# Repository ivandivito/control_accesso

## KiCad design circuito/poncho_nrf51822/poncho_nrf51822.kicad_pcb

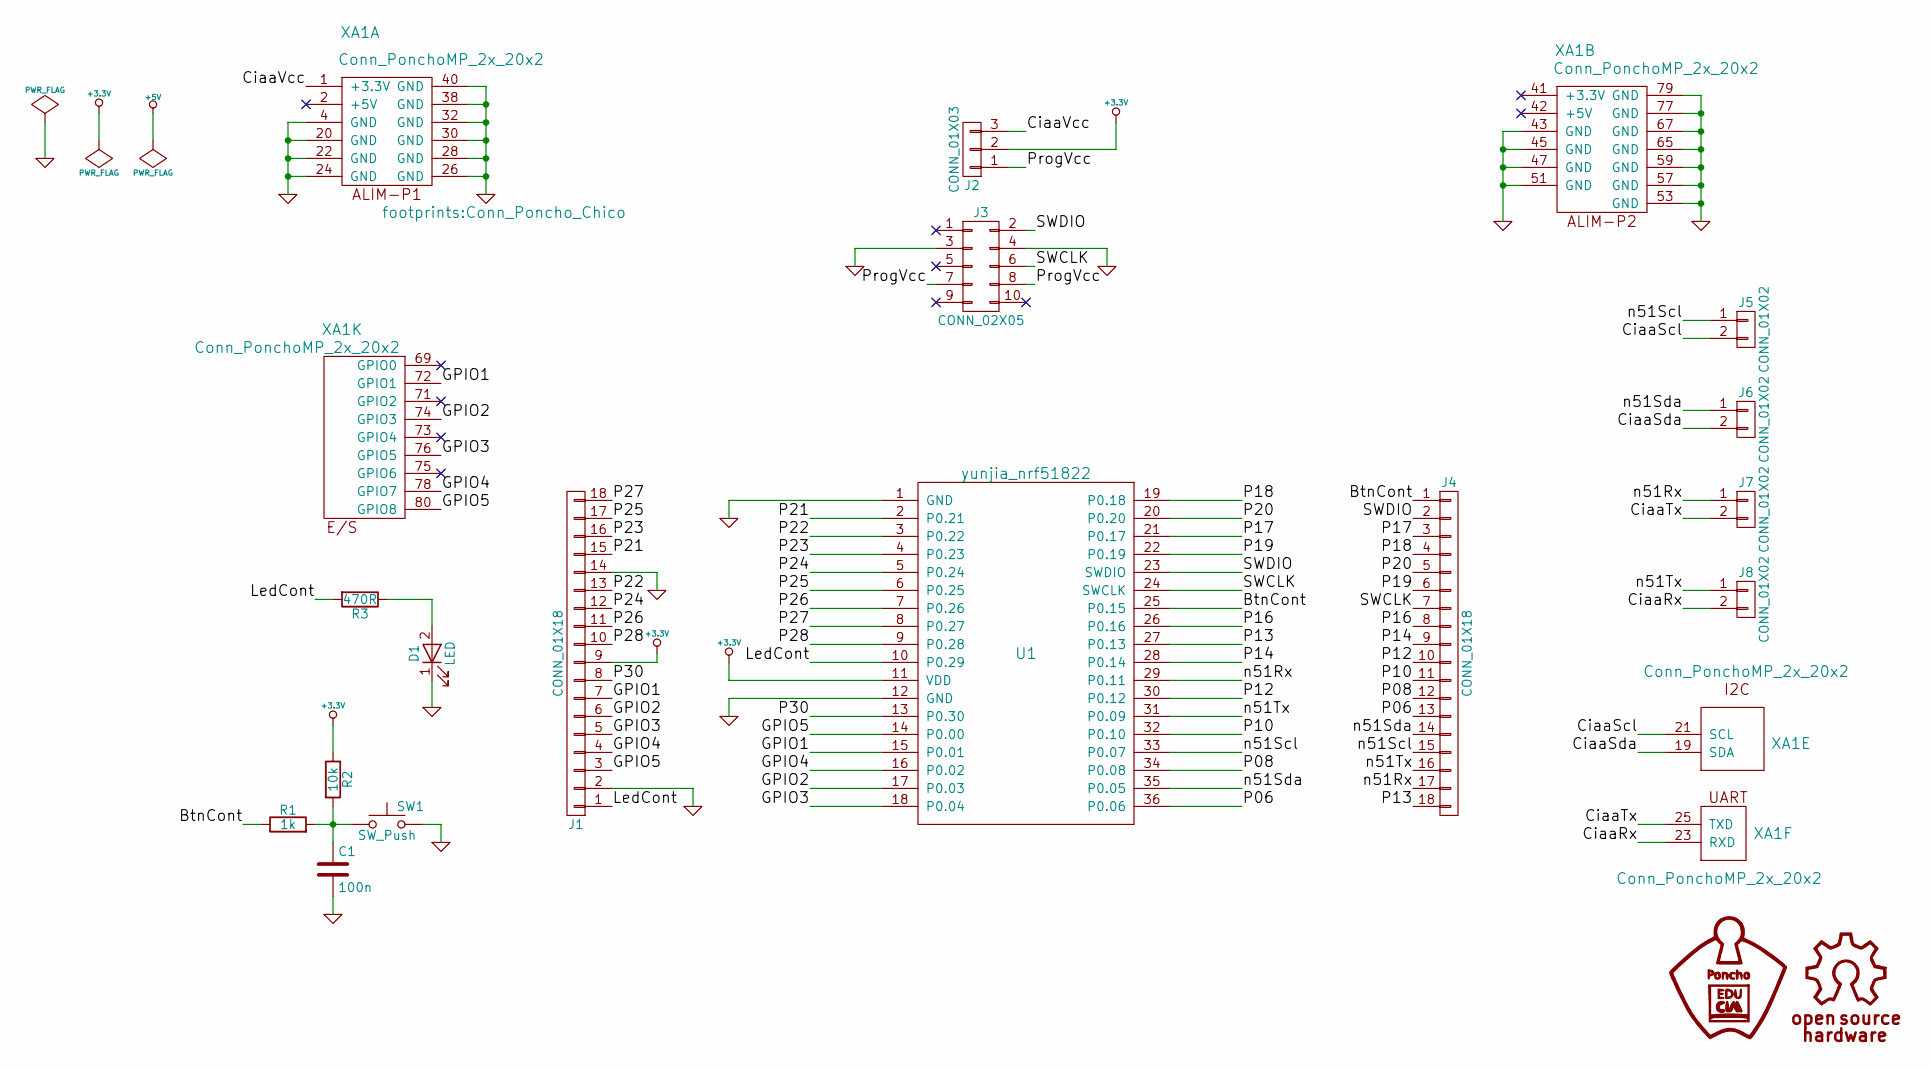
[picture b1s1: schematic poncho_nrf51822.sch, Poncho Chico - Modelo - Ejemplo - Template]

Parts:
C1: 100n; C_0805_HandSoldering
D1: LED; LED_D5.0mm
J1, J4: CONN_01X18; Pin_Header_Straight_1x18_Pitch2.54mm
J2: CONN_01X03; Pin_Header_Straight_1x03_Pitch2.54mm
J3: CONN_02X05; Pin_Header_Straight_2x05_Pitch2.54mm
J5, J6, J7, J8: CONN_01X02; Pin_Header_Straight_2x01_Pitch2.54mm
R1: 1k; R_0805_HandSoldering
R2: 10k; R_0805_HandSoldering
R3: 470R; R_0805_HandSoldering
SW1: SW_Push; SW_PUSH_6mm
U1: yunjia_nrf51822
XA1: Conn_PonchoMP_2x_20x2; Conn_Poncho_Chico

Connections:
+3.3V: J1.9, J2.2, R2.1, U1.11 (VDD)
/BtnCont: J4.1, R1.1, U1.25 (P0.15)
/CiaaRx: J8.2, XA1.23 (RXD)
/CiaaScl: J5.2, XA1.21 (SCL)
/CiaaSda: J6.2, XA1.19 (SDA)
/CiaaTx: J7.2, XA1.25 (TXD)
/CiaaVcc: J2.3, XA1.1 (+3.3V)
/GPIO1: J1.7, U1.15 (P0.01), XA1.72 (GPIO1)
/GPIO2: J1.6, U1.17 (P0.03), XA1.74 (GPIO3)
/GPIO3: J1.5, U1.18 (P0.04), XA1.76 (GPIO5)
/GPIO4: J1.4, U1.16 (P0.02), XA1.78 (GPIO7)
/GPIO5: J1.3, U1.14 (P0.00), XA1.80 (GPIO8)
/LedCont: J1.1, R3.2, U1.10 (P0.29)
/P06: J4.13, U1.36 (P0.06)
/P08: J4.12, U1.34 (P0.08)
/P10: J4.11, U1.32 (P0.10)
/P12: J4.10, U1.30 (P0.12)
/P13: J4.18, U1.27 (P0.13)
/P14: J4.9, U1.28 (P0.14)
/P16: J4.8, U1.26 (P0.16)
/P17: J4.3, U1.21 (P0.17)
/P18: J4.4, U1.19 (P0.18)
/P19: J4.6, U1.22 (P0.19)
/P20: J4.5, U1.20 (P0.20)
/P21: J1.15, U1.2 (P0.21)
/P22: J1.13, U1.3 (P0.22)
/P23: J1.16, U1.4 (P0.23)
/P24: J1.12, U1.5 (P0.24)
/P25: J1.17, U1.6 (P0.25)
/P26: J1.11, U1.7 (P0.26)
/P27: J1.18, U1.8 (P0.27)
/P28: J1.10, U1.9 (P0.28)
/P30: J1.8, U1.13 (P0.30)
/ProgVcc: J2.1, J3.7, J3.8
/SWCLK: J3.6, J4.7, U1.24 (SWCLK)
/SWDIO: J3.2, J4.2, U1.23 (SWDIO)
/n51Rx: J4.17, J7.1, U1.29 (P0.11)
/n51Scl: J4.15, J5.1, U1.33 (P0.07)
/n51Sda: J4.14, J6.1, U1.35 (P0.05)
/n51Tx: J4.16, J8.1, U1.31 (P0.09)
GND: C1.2, D1.1 (K), J1.2, J1.14, J3.3, J3.4, SW1.2, U1.1 (GND), U1.12 (GND), XA1.4 (GND), XA1.20 (GND), XA1.22 (GND), XA1.24 (GND), XA1.26 (GND), XA1.28 (GND), XA1.30 (GND), XA1.32 (GND), XA1.38 (GND), XA1.40 (GND), XA1.43 (GND), XA1.45 (GND), XA1.47 (GND), XA1.51 (GND), XA1.53 (GND), XA1.57 (GND), XA1.59 (GND), XA1.65 (GND), XA1.67 (GND), XA1.77 (GND), XA1.79 (GND)
unnamed: C1.1, R1.2, R2.2, SW1.1
unnamed: D1.2 (A), R3.1

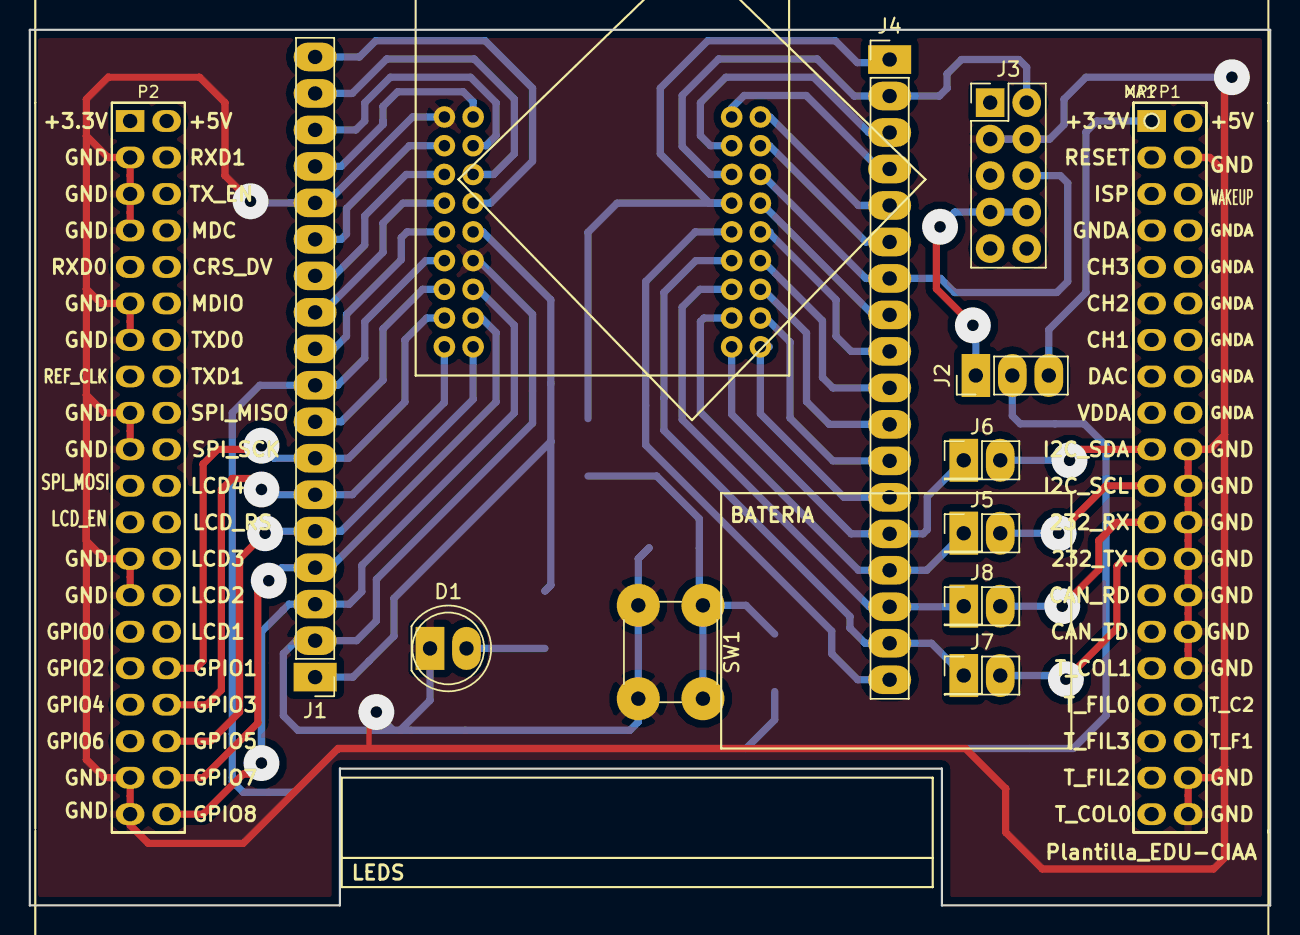
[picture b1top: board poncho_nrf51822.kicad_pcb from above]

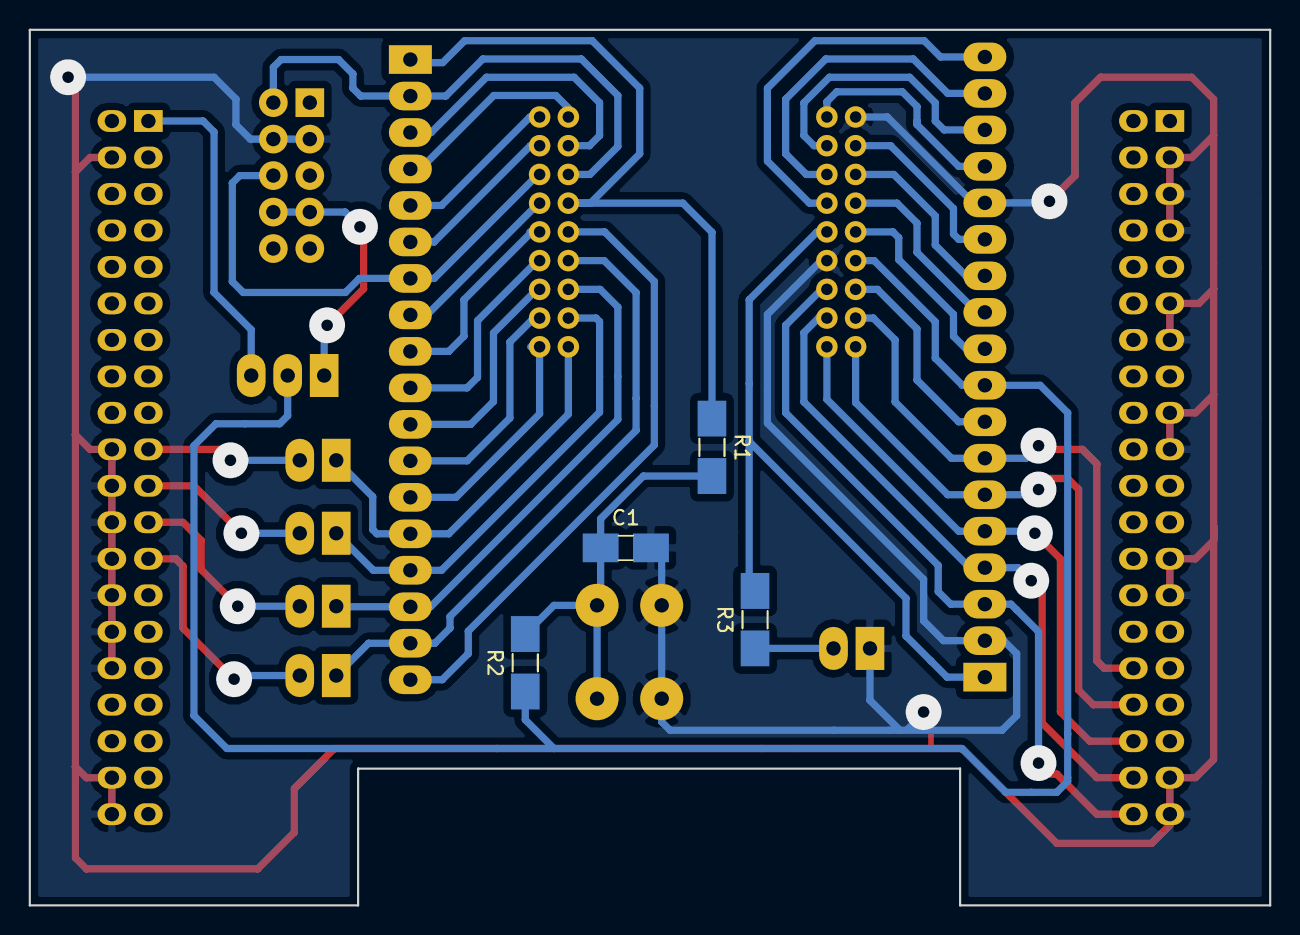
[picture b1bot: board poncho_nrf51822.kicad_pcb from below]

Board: 2 copper layers, 86.4 x 61.0 mm, 17 parts (4 on the bottom side), 43 nets.

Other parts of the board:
MP?: Plantilla_EDU-CIAA

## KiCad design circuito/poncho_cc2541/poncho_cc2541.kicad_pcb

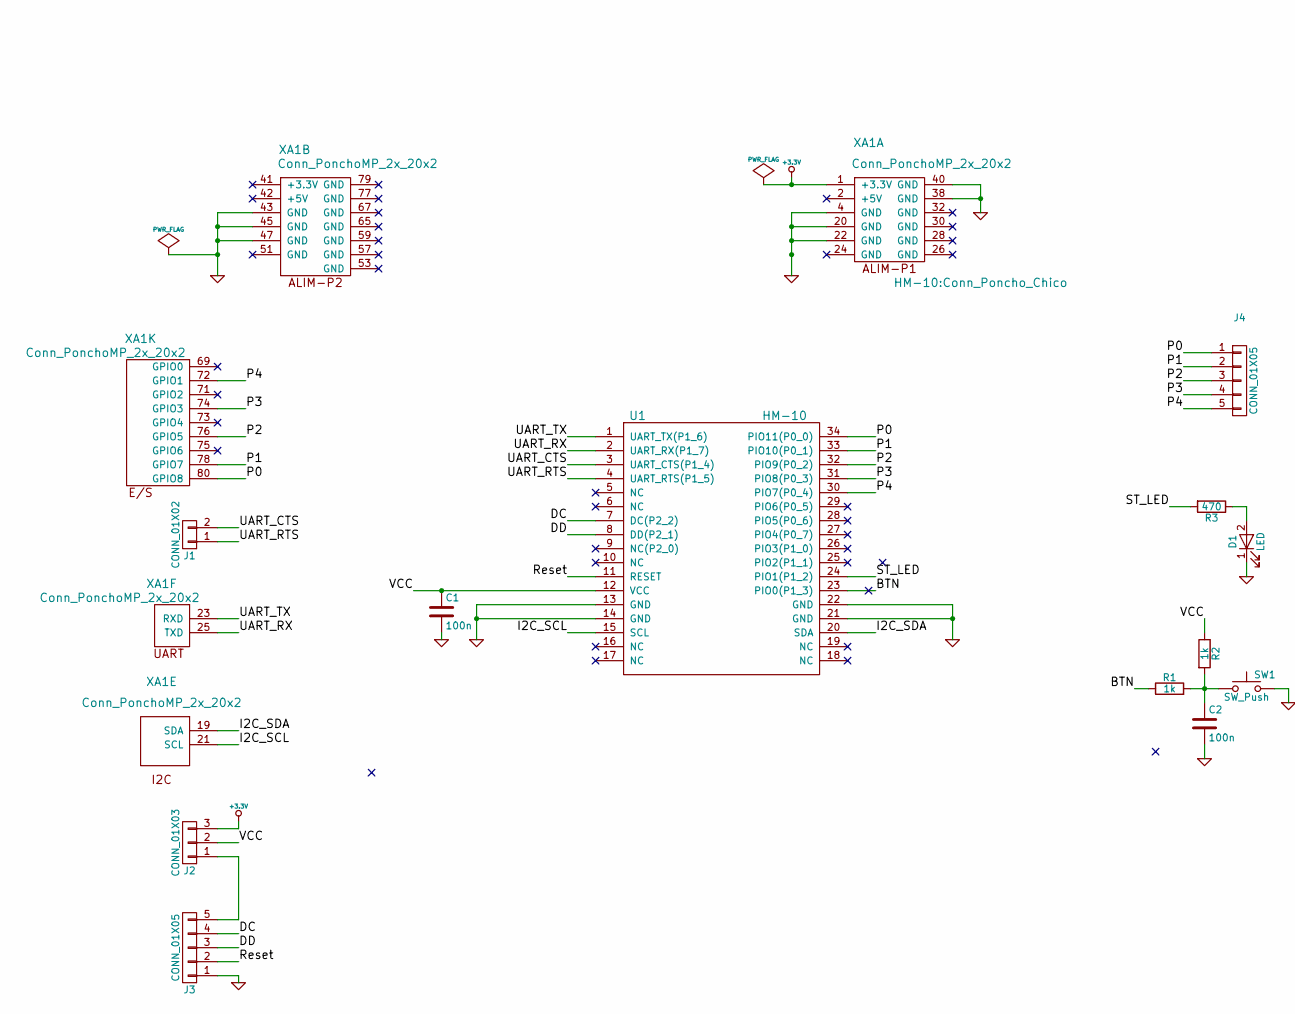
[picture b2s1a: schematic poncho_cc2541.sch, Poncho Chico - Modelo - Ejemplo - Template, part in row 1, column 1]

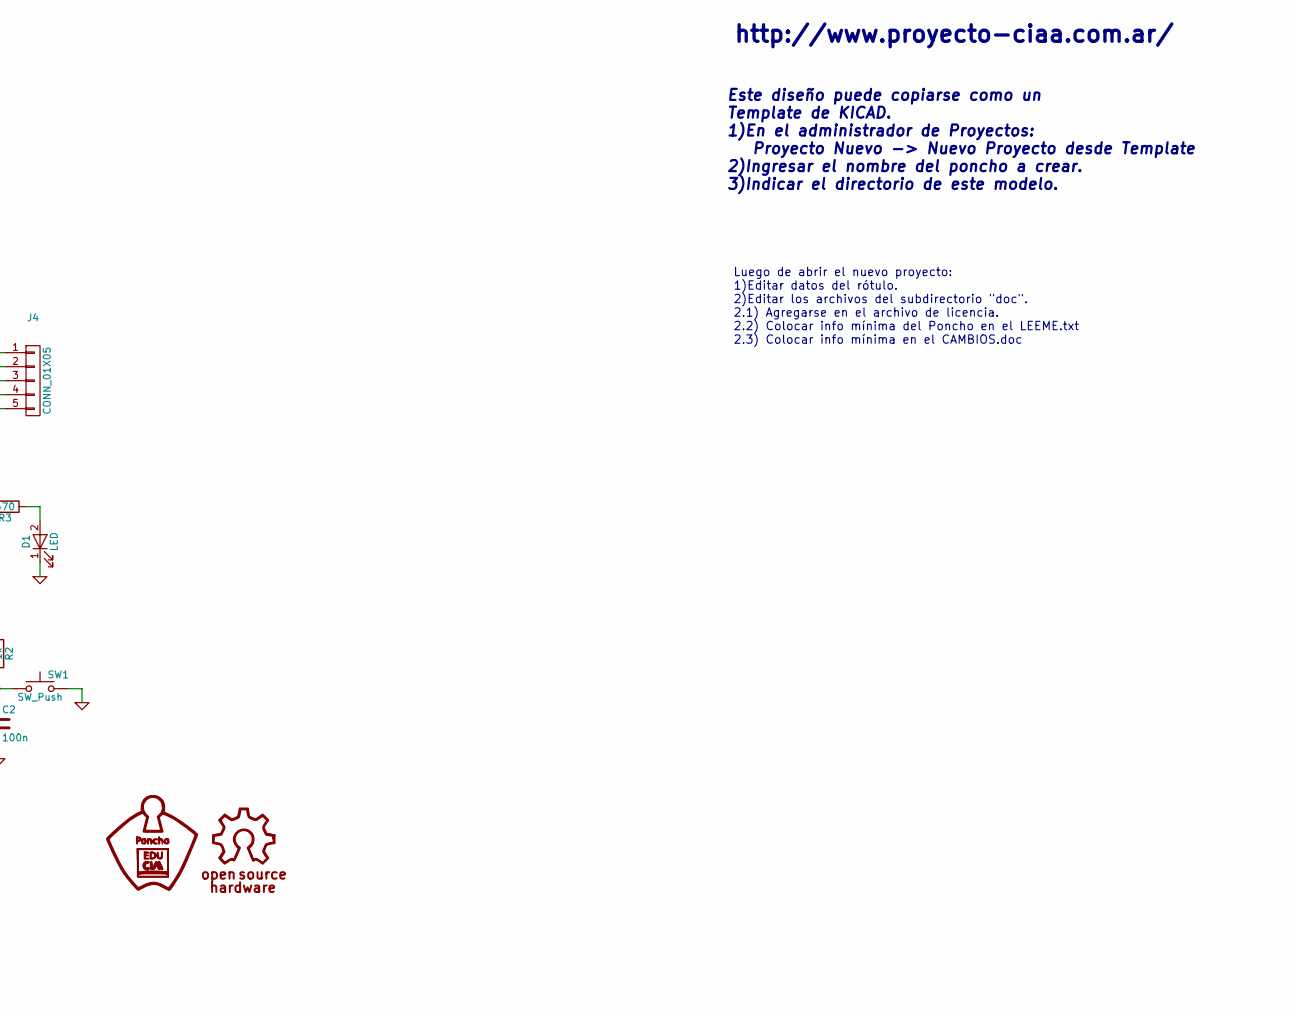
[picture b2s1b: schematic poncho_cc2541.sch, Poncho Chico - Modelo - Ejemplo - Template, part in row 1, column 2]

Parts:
C1, C2: 100n; C_Disc_D5.0mm_W2.5mm_P5.00mm
D1: LED; LED_D5.0mm
J1: CONN_01X02; Pin_Header_Straight_1x02_Pitch2.00mm
J2: CONN_01X03; Pin_Header_Straight_1x03_Pitch2.00mm
J3, J4: CONN_01X05; Pin_Header_Straight_1x05_Pitch2.00mm
R1, R2: 1k; R_Axial_DIN0207_L6.3mm_D2.5mm_P10.16mm_Horizontal
R3: 470; R_Axial_DIN0207_L6.3mm_D2.5mm_P10.16mm_Horizontal
SW1: SW_Push; SW_PUSH_6mm
U1: HM-10
XA1: Conn_PonchoMP_2x_20x2; Conn_Poncho_Chico

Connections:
+3.3V: J2.3, XA1.1 (+3.3V)
/BTN: R1.1, U1.23 (PIO0(P1_3))
/DC: J3.4, U1.7 (DC(P2_2))
/DD: J3.3, U1.8 (DD(P2_1))
/I2C_SCL: U1.15 (SCL), XA1.21 (SCL)
/I2C_SDA: U1.20 (SDA), XA1.19 (SDA)
/P0: J4.1, U1.34 (PIO11(P0_0)), XA1.80 (GPIO8)
/P1: J4.2, U1.33 (PIO10(P0_1)), XA1.78 (GPIO7)
/P2: J4.3, U1.32 (PIO9(P0_2)), XA1.76 (GPIO5)
/P3: J4.4, U1.31 (PIO8(P0_3)), XA1.74 (GPIO3)
/P4: J4.5, U1.30 (PIO7(P0_4)), XA1.72 (GPIO1)
/Reset: J3.2, U1.11 (RESET)
/ST_LED: R3.2, U1.24 (PIO1(P1_2))
/UART_CTS: J1.2, U1.3 (UART_CTS(P1_4))
/UART_RTS: J1.1, U1.4 (UART_RTS(P1_5))
/UART_RX: U1.2 (UART_RX(P1_7)), XA1.25 (TXD)
/UART_TX: U1.1 (UART_TX(P1_6)), XA1.23 (RXD)
/VCC: C1.1, J2.2, R2.1, U1.12 (VCC)
GND: C1.2, C2.2, D1.1 (K), J3.1, SW1.2, U1.13 (GND), U1.14 (GND), U1.21 (GND), U1.22 (GND), XA1.4 (GND), XA1.20 (GND), XA1.22 (GND), XA1.38 (GND), XA1.40 (GND), XA1.43 (GND), XA1.45 (GND), XA1.47 (GND)
unnamed: C2.1, R1.2, R2.2, SW1.1
unnamed: D1.2 (A), R3.1
unnamed: J2.1, J3.5

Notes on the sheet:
Este diseño puede copiarse como un Template de KICAD. 1)En el administrador de Proyectos: Proyecto Nuevo -> Nuevo Proyecto desde Template 2)Ingresar el nombre del poncho a crear. 3)Indicar el directorio de este modelo.
http://www.proyecto-ciaa.com.ar/
Luego de abrir el nuevo proyecto: 1)Editar datos del rótulo. 2)Editar los archivos del subdirectorio "doc". 2.1) Agregarse en el archivo de licencia. 2.2) Colocar info mínima del Poncho en el LEEME.txt 2.3) Colocar info mínima en el CAMBIOS.doc

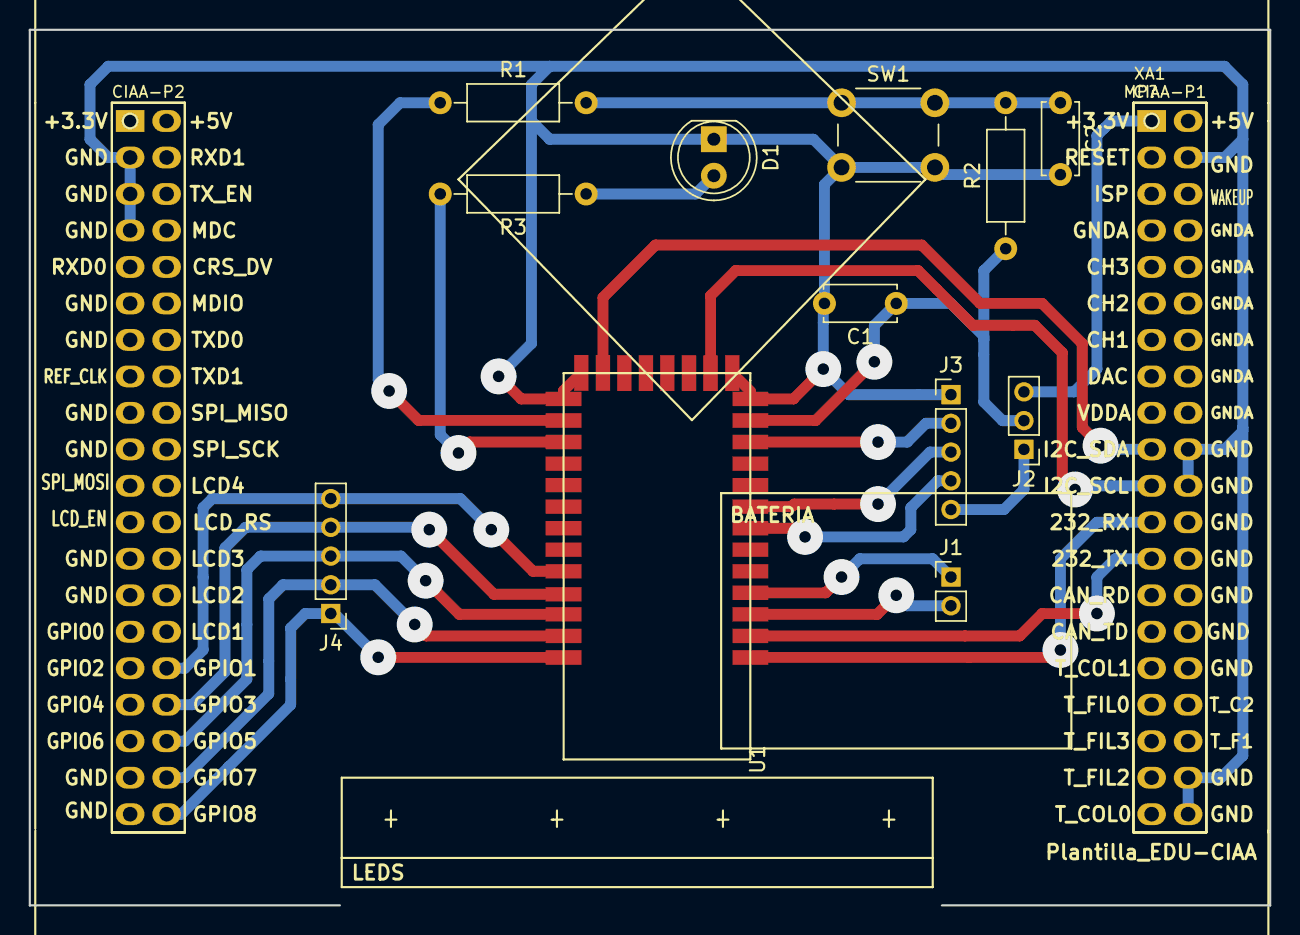
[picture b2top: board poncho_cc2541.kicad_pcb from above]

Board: 2 copper layers, 86.4 x 61.0 mm, 15 parts (0 on the bottom side), 22 nets.

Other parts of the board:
G101: Logo_OSHWA
MP?: Plantilla_EDU-CIAA

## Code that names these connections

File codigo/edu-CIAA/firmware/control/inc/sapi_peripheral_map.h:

/* Copyright 2015, Eric Pernia.
 * Copyright 2016, Ian Olivieri.
 * Copyright 2016, Eric Pernia.
 * All rights reserved.
 *
 * This file is part sAPI library for microcontrollers.
 *
 * Redistribution and use in source and binary forms, with or without
 * modification, are permitted provided that the following conditions are met:
 *
 * 1. Redistributions of source code must retain the above copyright notice,
 *    this list of conditions and the following disclaimer.
 *
 * 2. Redistributions in binary form must reproduce the above copyright notice,
 *    this list of conditions and the following disclaimer in the documentation
 *    and/or other materials provided with the distribution.
 *
 * 3. Neither the name of the copyright holder nor the names of its
 *    contributors may be used to endorse or promote products derived from this
 *    software without specific prior written permission.
 *
 * THIS SOFTWARE IS PROVIDED BY THE COPYRIGHT HOLDERS AND CONTRIBUTORS "AS IS"
 * AND ANY EXPRESS OR IMPLIED WARRANTIES, INCLUDING, BUT NOT LIMITED TO, THE
 * IMPLIED WARRANTIES OF MERCHANTABILITY AND FITNESS FOR A PARTICULAR PURPOSE
 * ARE DISCLAIMED. IN NO EVENT SHALL THE COPYRIGHT HOLDER OR CONTRIBUTORS BE
 * LIABLE FOR ANY DIRECT, INDIRECT, INCIDENTAL, SPECIAL, EXEMPLARY, OR
 * CONSEQUENTIAL DAMAGES (INCLUDING, BUT NOT LIMITED TO, PROCUREMENT OF
 * SUBSTITUTE GOODS OR SERVICES; LOSS OF USE, DATA, OR PROFITS; OR BUSINESS
 * INTERRUPTION) HOWEVER CAUSED AND ON ANY THEORY OF LIABILITY, WHETHER IN
 * CONTRACT, STRICT LIABILITY, OR TORT (INCLUDING NEGLIGENCE OR OTHERWISE)
 * ARISING IN ANY WAY OUT OF THE USE OF THIS SOFTWARE, EVEN IF ADVISED OF THE
 * POSSIBILITY OF SUCH DAMAGE.
 *
 */

/* Date: 2015-09-23 */

#ifndef _SAPI_PERIPHERALMAP_H_
#define _SAPI_PERIPHERALMAP_H_

/*==================[inclusions]=============================================*/

#include "../../control/inc/sapi_datatypes.h"

/*==================[cplusplus]==============================================*/

#ifdef __cplusplus
extern "C" {
#endif

/*==================[macros]=================================================*/

/*==================[typedef]================================================*/

/* ----- Begin Pin Config Structs NXP LPC4337 ----- */

typedef struct{
   int8_t port;
   int8_t pin;
} pinConfigLpc4337_t;

/* ------ End Pin Config Structs NXP LPC4337 ------ */


/* ------- Begin EDU-CIAA-NXP Peripheral Map ------ */

/* Defined for sapi_gpio.h */
typedef enum{
   /* EDU-CIAA-NXP */

   // P1 header
   T_FIL1,    T_COL2,    T_COL0,    T_FIL2,      T_FIL3,  T_FIL0,     T_COL1,
   CAN_TD,    CAN_RD,    RS232_TXD, RS232_RXD,

   // P2 header
   GPIO8,     GPIO7,     GPIO5,     GPIO3,       GPIO1,
   LCD1,      LCD2,      LCD3,      LCDRS,       LCD4,
   SPI_MISO,
   ENET_TXD1, ENET_TXD0, ENET_MDIO, ENET_CRS_DV, ENET_MDC, ENET_TXEN, ENET_RXD1,
   GPIO6,     GPIO4,     GPIO2,     GPIO0,
   LCDEN,
   SPI_MOSI,
   ENET_RXD0,

   // Switches
   // 36     37     38     39
   TEC1,  TEC2,  TEC3,  TEC4,

   // Leds
   // 40     41     42     43     44     45
   LED1,  LED2,  LED3,  LEDR,  LEDG,  LEDB,

   /* CIAA-NXP */
 /* 46     47     48     49     50     51     52     53 */
   DI0,   DI1,   DI2,   DI3,   DI4,   DI5,   DI6,   DI7,
 /* 54     55     56     57     58     59     60     61 */
   DO0,   DO1,   DO2,   DO3,   DO4,   DO5,   DO6,   DO7
} gpioMap_t;

/* Defined for sapi_adc.h */
typedef enum{
/* 62         63       64        65       */
   AI3 = 62, AI2 = 63, AI1 = 64, AI0 = 65,
             CH3 = 63, CH2 = 64, CH1 = 65
/*  46        47   48  49 */
// AI2 = 46, AI1, AI0, AO
} adcMap_t;

/* Defined for sapi_dac.h */
typedef enum{
/* 66 */
   AO = 66,
   DAC = 66
} dacMap_t;

/* Defined for sapi_uart.h */
typedef enum{
   UART_USB, UART_232, UART_485
} uartMap_t;

/*Defined for sapi_timer.h*/
//NOTE: if servo is enable (servoConfig used) the only available timer to use is TIMER0
typedef enum{
   TIMER0, TIMER1, TIMER2, TIMER3
} timerMap_t;
typedef enum{
   TIMERCOMPAREMATCH0, TIMERCOMPAREMATCH1, TIMERCOMPAREMATCH2, TIMERCOMPAREMATCH3
} timerCompareMatch_t;

/*Defined for sapi_sct.h*/
// NOTE: CTOUT11 has no SCT mode associated, so it can't be used!
// NOTE: if pwm is enable (pwmConfig used) there will be no sct channels available
typedef enum{
   CTOUT0, CTOUT1, CTOUT2, CTOUT3, CTOUT4, CTOUT5, CTOUT6, CTOUT7, CTOUT8,
   CTOUT9, CTOUT10, CTOUT11, CTOUT12, CTOUT13
} sctMap_t;

/*Defined for sapi_pwm.h*/
typedef enum{
   PWM0, PWM1, PWM2, PWM3, PWM4, PWM5, PWM6, PWM7, PWM8, PWM9, PWM10
} pwmMap_t;

/*Defined for sapi_servo.h*/
typedef enum{
   SERVO0, SERVO1, SERVO2, SERVO3, SERVO4, SERVO5, SERVO6, SERVO7, SERVO8
} servoMap_t;

/*Defined for sapi_i2c.h*/
/* Comment because already defined in "i2c_18xx_43xx.h"*/
/*
typedef enum{
   I2C0 // TODO: Add support for I2C1
} i2cMap_t;
*/
typedef uint8_t i2cMap_t;

/* ------- End EDU-CIAA-NXP Peripheral Map -------- */

/*==================[external data declaration]==============================*/

/*==================[external functions declaration]=========================*/

/*==================[cplusplus]==============================================*/

#ifdef __cplusplus
}
#endif

/*==================[end of file]============================================*/
#endif /* #ifndef _SAPI_PERIPHERALMAP_H_ */

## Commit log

2017-05-07 inicial
2017-05-18 placa
2017-05-21 poncho echo
2017-05-25 agrego codigo nrf51822 mbed
2017-05-25 ordeno
2017-05-29 add beacon reader code
2017-05-29 add beacon serial com
2017-06-01 agrego firmware edu ciaa
2017-06-03 primera version con malloc
2017-06-10 funcionando
2017-06-13 arreglo cmake
2017-06-13 arreglo error de preambulo de ibeacon
2017-06-18 eeprom funcionando
2017-06-18 eeprom funcionando fix
2017-06-20 agrego callbacks
2017-06-21 agrego programa de pc
2017-06-21 arreglo error de inicio y cambio logo
2017-06-21 cambio nombre de app
2017-06-21 arreglo error del jar
2017-06-21 modifico prioridades
2017-06-26 agrego informes
